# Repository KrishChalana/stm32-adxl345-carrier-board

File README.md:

# STM32-ADXL343 Carrier Board

A custom 4-layer-ready KiCad PCB (v2) built around a bare **STM32F411CE** microcontroller and an **ADXL343** 3-axis accelerometer over I2C. It has an onboard 12V-to-3.3V buck converter, USB micro-B, SWD debug header and a UART header. Designed as the hardware companion to my [bare-metal STM32 driver work](https://github.com/KrishChalana/stm32-bare-metal-drivers), moving the same STM32 + accelerometer setup from breadboard to an integrated board.

**Status:** Schematic v2 complete (KiCad 10). Design files only, not yet fabricated.

## Overview

The board takes a nominal **12V input** through a screw terminal, protects it, and steps it down to **3.3V** with an MP2359 buck converter. That rail powers the STM32F411 and the ADXL343. The MCU is the bare STM32F411CEU6 (UFQFPN48) with its own crystal, reset, boot and decoupling circuitry, rather than a Black Pill module. The ADXL343 sits on I2C2 and is fixed in I2C mode in hardware.

## Repo contents

- KiCad schematic (`.kicad_sch`)
- KiCad PCB layout (`.kicad_pcb`)
- `renders/`: schematic, routed PCB and 3D render screenshots

## Screenshots

### Schematic

### Routed PCB

### 3D Render

## Related

- [STM32 Bare-Metal Drivers](https://github.com/KrishChalana/stm32-bare-metal-drivers): register-level GPIO, UART, timers, ADC
- [ADXL345 I2C/SPI Driver](https://github.com/KrishChalana/ADXL345-Drivers): sensor driver used with this board

## Author

Krish Chalana ([@KrishChalana](https://github.com/KrishChalana))

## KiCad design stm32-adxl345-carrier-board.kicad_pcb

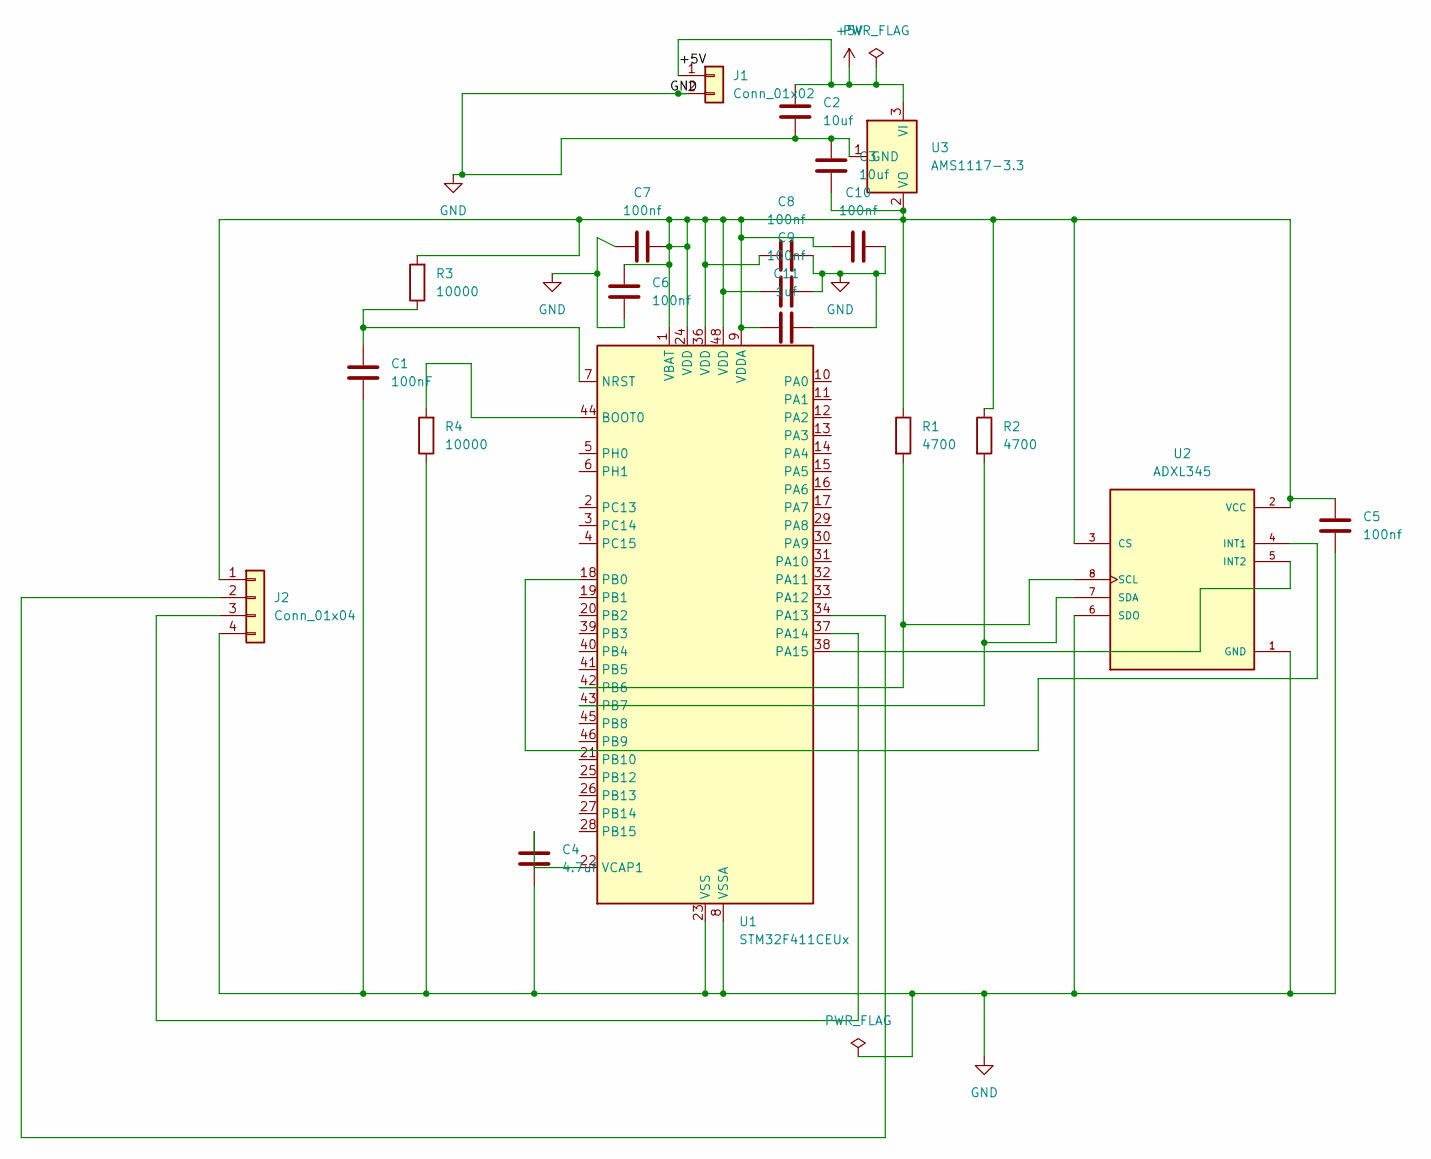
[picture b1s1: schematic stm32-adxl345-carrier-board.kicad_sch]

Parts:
C1: 100nF; C_0504_1310Metric
C2, C3: 10uf; C_0504_1310Metric
C4: 4.7uf; C_0504_1310Metric
C5, C6, C7, C8, C9, C10: 100nf; C_0504_1310Metric
C11: 1uf; C_0504_1310Metric
J1: Conn_01x02; PinHeader_1x02_P2.54mm_Vertical
J2: Conn_01x04; PinHeader_1x04_P2.54mm_Vertical
R1, R2: 4700; R_0805_2012Metric
R3, R4: 10000; R_0805_2012Metric
U1: STM32F411CEUx; QFN-48-1EP_7x7mm_P0.5mm_EP5.6x5.6mm
U2: ADXL345; MODULE_SEN-09836; PARTREV v14
U3: AMS1117-3.3; SOT-223-3_TabPin2

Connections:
+5V: C2.1, J1.1, U3.3 (VI)
GND: C1.2, C2.2, C3.1, C4.2, C5.2, C6.2, C7.1, C8.2, C9.2, C10.2, C11.2, J1.2, J2.4, R4.1, U1.8 (VSSA), U1.23 (VSS), U1.35 (VSS), U1.47 (VSS), U1.49 (VSS), U2.1 (GND), U2.6 (SDO), U3.1 (GND)
unnamed: C3.2, C5.1, C6.1, C7.2, C8.1, C9.1, C10.1, C11.1, J2.1, R1.1, R2.1, R3.2, U1.1 (VBAT), U1.9 (VDDA), U1.24 (VDD), U1.36 (VDD), U1.48 (VDD), U2.2 (VCC), U2.3 (CS), U3.2 (VO)
unnamed: J2.2, U1.34 (PA13)
unnamed: J2.3, U1.37 (PA14)
unnamed: R4.2, U1.44 (BOOT0)
unnamed: C1.1, R3.1, U1.7 (NRST)
unnamed: U1.38 (PA15), U2.5 (INT2)
unnamed: U1.18 (PB0), U2.4 (INT1)
unnamed: R1.2, U1.42 (PB6), U2.8 (SCL)
unnamed: R2.2, U1.43 (PB7), U2.7 (SDA)
unnamed: C4.1, U1.22 (VCAP1)

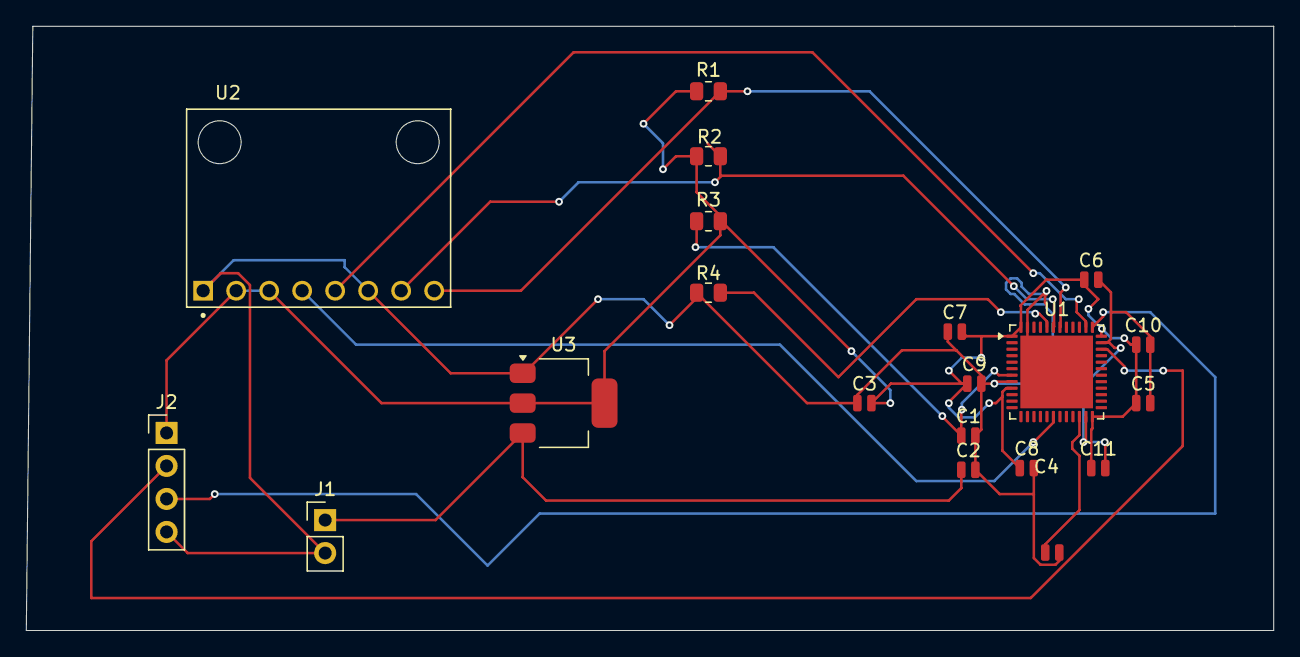
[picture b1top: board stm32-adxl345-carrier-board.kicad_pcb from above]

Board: 2 copper layers, 96.0 x 46.5 mm, 20 parts (0 on the bottom side), 12 nets.
